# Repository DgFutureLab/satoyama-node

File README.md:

satoyama-node
=============

Satoyama Sensor Network node stack. This stack is designed to connect chibis and sabotens to <a href="https://github.com/DgFutureLab/satoyama-api">Satoyama API</a>. Created by <a href="http://fljapan.com/">Future Lab</a> based on <a href="http://www.freaklabsstore.com">Freaklabs open hardware</a>.

# Prerequisites

## Hardware
(List of provided parts: board, sensors, batteries, etc.)

(NOTE: Add mark on saboten board to connect the FTDI Breakout board in the right direction!!)

## Software
1. Arduino IDE 1.0.6 (Does not work with Arduino 1.5.8 BETA). Get it <a href="http://www.arduino.cc/">here</a>
2. git

# Installation
Follow these steps to set up a Satoyama sensor node!
## Get the code
1. Download this repository: $ git clone https://github.com/DgFutureLab/satoyama-node.git
2. Go into the new directory: $ cd satoyama-node
3. Download all the libraries: $ git pull && git submodule init && git submodule update && git submodule status

## Prepare Arduino libraries

Import the required libraries into your Arduino IDE:  

1. satoyama-libs/SatoyamaChibiLib 
2. satoyama-libs/SdFat 
3. satoyama-libs/chibiArduino-master
4. satoyama-libs/PCF2127
5. satoyama-libs/Humidity_Temperature_Sensor
6. satoyama-libs/NewPing

If you use the standard Arduino GUI, go to Sketch → Import Library → Add Library and select each library name folder.

For the Saboten board: 

1. Copy the folder 'mighty-1284p-freaklabs' inside satoyama-libs to a folder called 'hardware' off your sketches directory, e.g. /Users/maniacbug/Source/Arduino/hardware/mighty-1284p
In a Mac environment: Arduino.app/contents/resources/Java/hardware/
2. Restart the IDE
3. Select Tools > Board > Freaklabs Saboten...

## Prepare the hardware

1. Attach a sonnar, a temperature sensor and a humidity sensor. The pin numbers are specified in <a href="https://github.com/DgFutureLab/satoyama-node/blob/master/SatoyamaChibiLib/config.h">this file</a> (6 for sonar, 0 for temp/humidity)
2. Connect the board to the computer
 
-In case of the Saboten:
Check that the FTDI Breakout board switch is on 5V

3. For OSX users, download the FTDI drivers from http://www.ftdichip.com/Drivers/VCP.htm

4. Open test_saboten/test_saboten.ino (for saboten)
4. Open File>Examples>Chibiarduino-master>4.cmdline (for Chibi)
5. Select your board on the dropdown menu Tool>Board>(FreakLabs Saboten for the saboten) or (Arduino Pro or ProMini (3.3V, 8MHz) w/ATmega328)
6. Upload it to the board
7. Open Arduino IDE's Serial Monitor
8. Set the communication to Carriage return and 57600 baud
9. Set the short address of this collector node by hand writing   *setsaddr* \<address\>  in the serial monitor command prompt. The address should be in HEXADECIMAL. (The address is currently (as of Jan, 2015) set via the script in satoyama-konohana) 
9. Upload collector/collector.ino into your Saboten board. (Include all the necessary libs from third-party-libs folder)

## Setup build system with CMake
Before we wrote the sketches using the Arduino GUI, but now we use standard CMake to generate make files.

1. Install CMake (e.g. brew install cmake on OSX)
2. Change directory into the folder containing the source code that you want to run on the board.
3. mkdir build (all the build files will be stored in this directory)
4. Navigate to build directory: cd build 
5. compile source code and upload to the device: cmake .. -Wno-dev && make && make upload (make sure that the build directory is empty, as CMake will complain otherwise)
6. Use screen to monitor output from the serial device (e.g. tty.usbserial-A501K9HW): /dev/tty.usbserial-A501K9HW 57600,sc8

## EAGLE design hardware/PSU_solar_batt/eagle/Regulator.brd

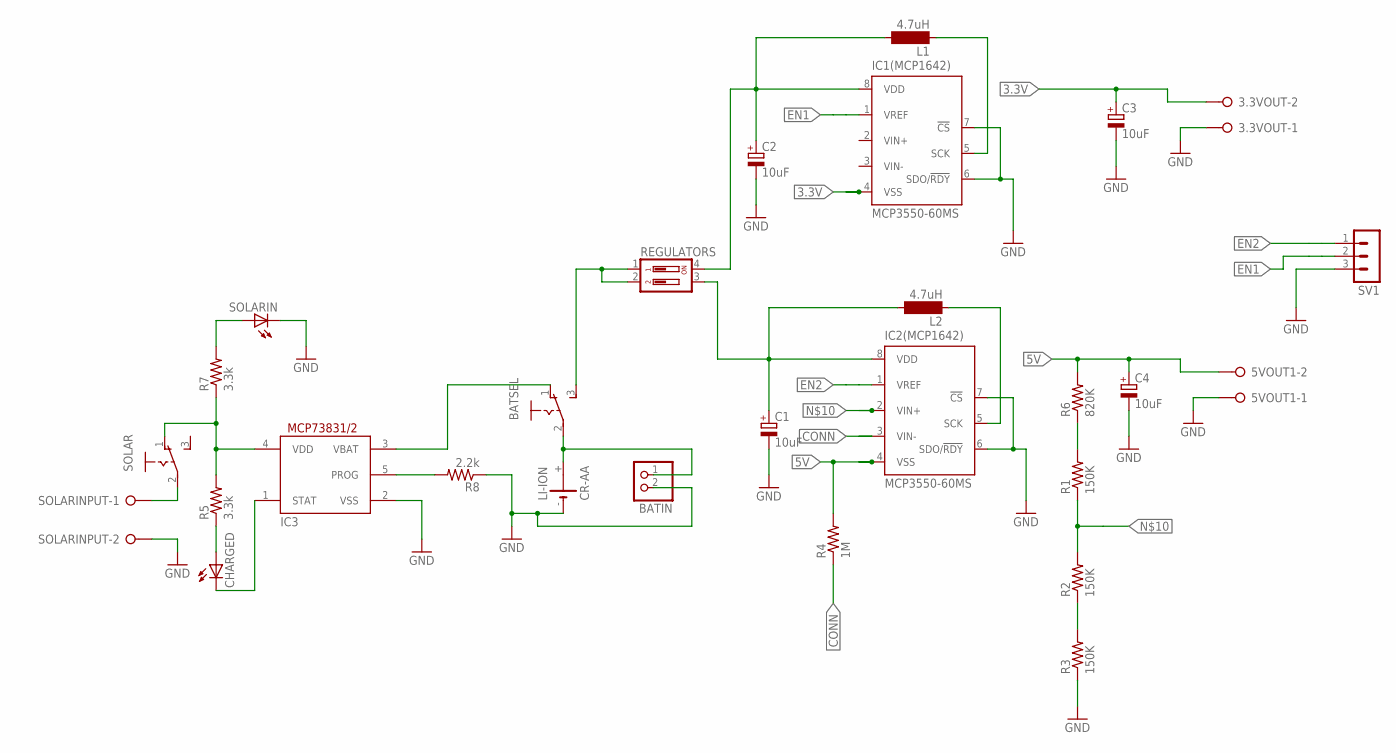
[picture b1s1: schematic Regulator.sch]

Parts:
3.3VOUT, 5VOUT1: W237-02P; W237-132
BATIN: JST_2PIN-THM; JST-PH-2-THM
BATSEL: 255SB
C1, C2, C3, C4: 10uF; 140CLH-1010
CHARGED: LEDCHIP-LED0603; CHIP-LED0603
IC1(MCP1642), IC2(MCP1642): MCP3550-60MS; MSOP8
IC3: MCP73831/OT; SOT23-5L
L1, L2: 4.7uH; MS85
LI-ION: CR-AA; CRAA
R1, R2, R3: 150K; M0805
R4: 1M; M0805
R5, R7: 3.3k; M3216
R6: 820K; M0805
R8: 2.2k; M3216
REGULATORS: DIP02YL
SOLAR: 255SB
SOLARIN: LEDCHIP-LED0603; CHIP-LED0603
SOLARINPUT: W237-02P; W237-132
SV1: MA03-1

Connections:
3.3V: 3.3VOUT.2, C3.+, IC1(MCP1642).4 (VSS)
5V: 5VOUT1.2, C4.+, IC2(MCP1642).4 (VSS), R4.2, R6.2
CONN: IC2(MCP1642).3 (VIN-), R4.1
EN1: IC1(MCP1642).1 (VREF), SV1.2
EN2: IC2(MCP1642).1 (VREF), SV1.1
MCP1642: C2.+, IC1(MCP1642).8 (VDD), L1.2, REGULATORS.4
unnamed: IC1(MCP1642).5 (SCK), L1.1
unnamed: R1.2, R6.1
unnamed: IC2(MCP1642).5 (SCK), L2.1
unnamed: R2.1, R3.2
unnamed: C1.+, IC2(MCP1642).8 (VDD), L2.2, REGULATORS.3
unnamed: IC3.4 (VDD), R5.2, R7.1, SOLAR.1 (O)
unnamed: IC2(MCP1642).2 (VIN+), R1.1, R2.2
unnamed: CHARGED.A, R5.1
unnamed: CHARGED.C, IC3.1 (STAT)
unnamed: BATSEL.3 (S), REGULATORS.1, REGULATORS.2
unnamed: R7.2, SOLARIN.A
unnamed: IC3.5 (PROG), R8.2
unnamed: BATSEL.1 (O), IC3.3 (VBAT)
unnamed: 3.3VOUT.1, 5VOUT1.1, BATIN.2 (1), C1.-, C2.-, C3.-, C4.-, IC1(MCP1642).6 (SDO/!RDY), IC1(MCP1642).7 (!CS), IC2(MCP1642).6 (SDO/!RDY), IC2(MCP1642).7 (!CS), IC3.2 (VSS), LI-ION.-, R3.1, R8.1, SOLARIN.C, SOLARINPUT.2, SV1.3
unnamed: SOLAR.2, SOLARINPUT.1
unnamed: BATIN.1 (2), BATSEL.2, LI-ION.+

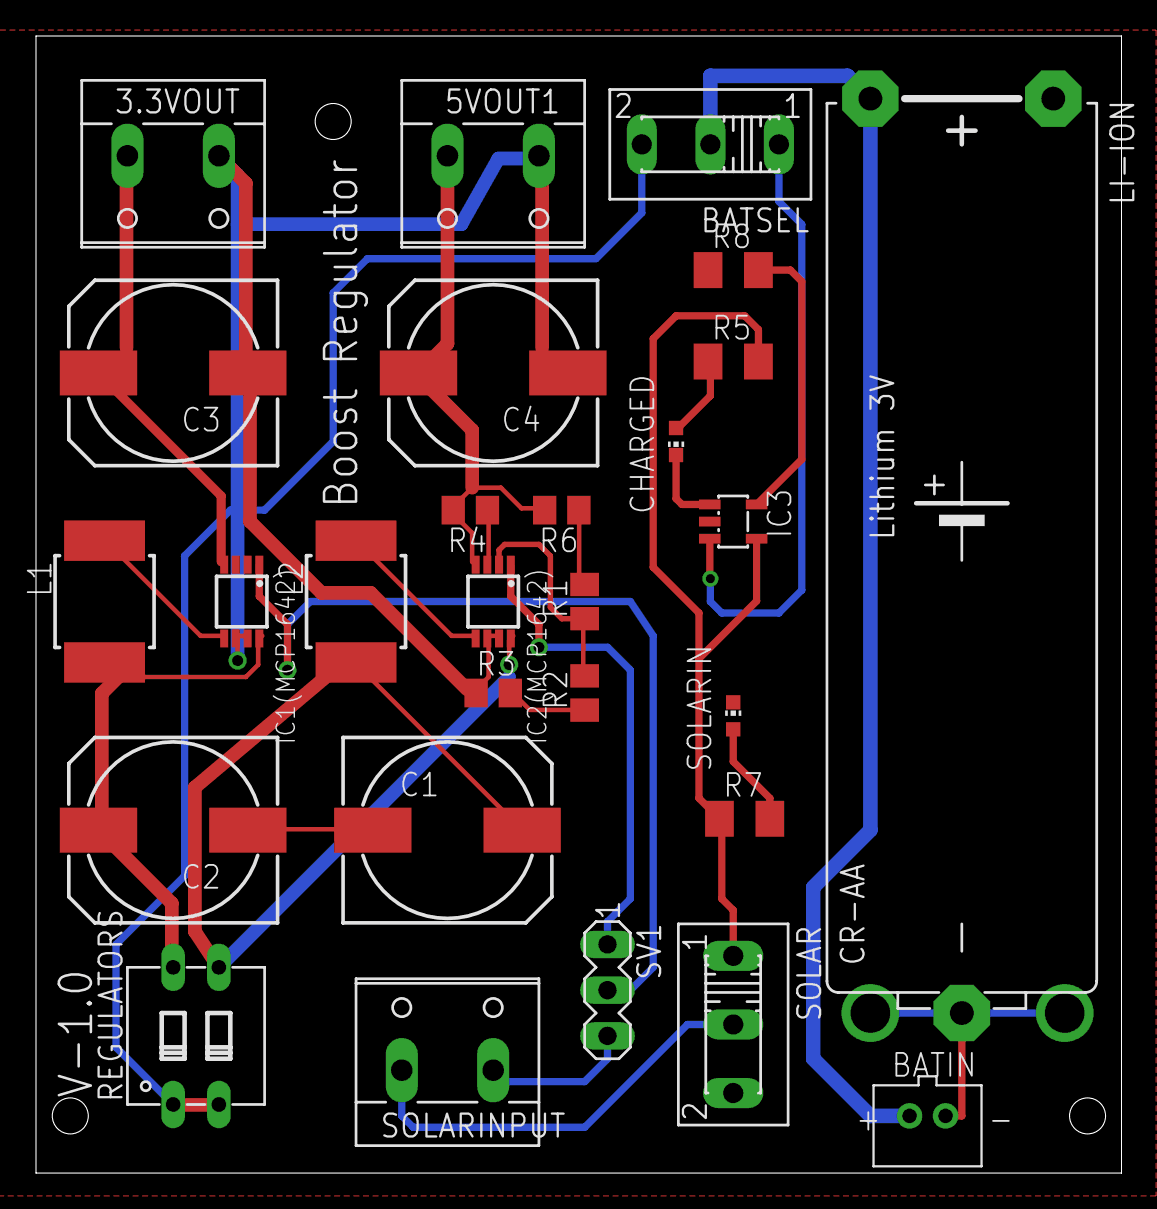
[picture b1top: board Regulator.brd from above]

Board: 2 copper layers, 60.3 x 63.2 mm, 28 parts (0 on the bottom side), 22 nets.

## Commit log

2014-12-03 Collector code
2014-12-03 Arduino library code added
2014-12-05 Moving library
2014-12-05 Cleaning code
2014-12-05 Changing satoyamachibilib defines
2014-12-05 Changed step one
2014-12-16 Adds libs as submodule
2014-12-16 Adds set short address function in collector sketch
2014-12-16 Reverts collector sketch
2014-12-16 deleted third party libs folder
2015-01-07 Fixes path
2015-01-07 Adds pin definitions for VBAT and VSOL
2015-01-07 Creates new ricefield node sketch && renames generic collector sketch to basic
2015-01-07 Fixes cope script
2015-01-08 Sensor node now sends battery voltage as well
2015-01-23 Adds design files for node front
2015-01-23 Adds some sketches for testing the rtc
2015-01-27 Testing second interrupt
2015-01-27 Second interrupt works!
2015-01-27 Interrupt works!! Arduino get it!
2015-01-28 Adds working sleep cycle sketch!
2015-01-28 Saboten is now woken up after 1 minute of sleep
2015-01-29 Adds saboten schematic v1.1
2015-01-30 Instruction for Takachi
2015-02-04 Removes variable number of arguments from sleepRadio function
2015-02-04 Inserts pointer for debugging purposes
2015-02-05 Adding all the power management functions to the collector code
2015-02-05 Remove SatoyamaChibiLib
2015-02-09 Fuck-it-commit. Shit aint working for now.
2015-02-09 Adds CMake script for sleep_cycle program
2015-02-10 Adds header file for sleep cycle program
2015-02-10 Fixes header file. sleep_cycle.cpp now compiles, but all calls to pcf code is commented out
2015-02-10 sleep_cycle now compiles with rtc functions
2015-02-10 Moves around some stuff
2015-02-10 Adds gitignore
2015-02-10 Updates gitignore to ignore all build directories
2015-02-10 Modifies gitignore
2015-02-18 Added description
2015-02-19 Includes temp and sonar libs
2015-02-19 Adds sensor reading to power managed code
2015-02-19 Ricefield sketch compiles, but hangs when trying to transmit data
2015-02-19 BOOM! Working ricefield sketch with power management.
2015-03-03 Cleans and refactors ricefield code
2015-03-25 Surpresses compile time warnings
2015-03-25 Program now uses Saboten library. Confirmed that sleep cycle still works.
2015-03-25 Fixes attachInterrupt in setup && deletes old code
2015-03-25 Adds function to read battery voltage
2015-03-26 Ricefield sketch is now using library function to read battery level
2015-03-26 reicefield program uses cpp lib function
2015-03-26 Removes functions that have been moved to library
2015-03-30 ricefield.cpp works with satoyama-libs da4f78607ab67df42064779d6855fbd5850ac329
2015-03-31 moves board specific setup to board constructor
2015-03-31 Initializes board as pointer
2015-03-31 Refactors and cleans
2015-04-01 ricefield sketch working with satoyama-libs b6a387567a011a091c9add9ea261f50329c236da
2015-04-03 Wifi test
2015-04-07 Removes comments
2015-04-07 Fixes compillation errors
2015-04-08 Adds saboten_sleep sketch (old code, but for reference)
2015-04-08 SD card detection works
2015-04-08 Successfully writes dummy data to SD card
2015-04-09 Fixed bug where file was not opened roperly at random times
2015-04-09 Ricefield sketch now stores battery voltage to SD card
2015-04-10 Adds FILENAME as define in start of program
2015-04-10 Commits changes in satoyama-libs
2015-04-10 Switches to using Saboten function for reading diagnostics (such as voltage level)
2015-04-10 Commits changes in libs
2015-04-10 Finally posting
2015-04-17 Added reading from the actual sensor, and changed to new post and get functions
2015-04-21 Saboten schematics
2015-04-24 Ricefield program with sonar
2015-04-24 Updates libraries
2015-04-27 Checkout here to get code for self-contained sensor node
2015-04-30 adds function for timestamp
2015-04-30 Adds set timestamp function && writes initial time to SD card
2015-04-30 Checkout this commit to get timestamps on data
2015-05-14 Adds sleep loop && memset
2015-05-14 Adds LTSpice simulation of basic negative feedback opamp circuit
2015-05-14 Adds simulation of opamp with bias voltage on positive input
2015-05-19 Adds old arduino version of ricefield sketch for Togas demo at Solid.
2015-05-19 Adds the 3d model of the sonar protector designed by Risa
2015-05-21 Adds chibi version of ricefield sketch. Does not compile with CMake yet though
2015-05-21 Adds snapshots of Daikis first idea for node enclosure
2015-06-08 Adds schematic for TX/RX ultrasonic range finder
2015-06-08 Adds simulation of TX circuit using pulse generator model
2015-06-08 Adds simulation of TX circuit using 555 to generate pulse train
2015-06-09 Renames schematics folder to hardware
2015-06-09 Adds BOM for design1
2015-06-09 Renames folder to simulation
2015-06-09 TX circuit now uses 2N2222 model instead of generic NPN model
2015-06-09 Adds 2N2222 model
2015-06-09 Updates .gitignore to ignore LTSpice aux files
2015-07-17 Adds first ricefield data!!
2015-07-19 Adds schematic/simulation of circuitry to switch between TX and RX modes in the sonar
2015-07-19 Adds TX circuit based on H bridge configuration
2015-07-20 Adds LTSpice file with TX circuit and simulated RX signal, with a signal that switches transducer between TX and RX modes
2015-07-20 Renames signals
2015-07-21 Adds active lowpass filter with cap to remove DC offset from signal
2015-07-21 Fixes faulty wiring of transistor for VCC enable
2015-07-22 Adds first stage amp with LPF, removes unused voltage sources and rearranges
2015-07-24 Moves sd code out of the ricefield sketch
2015-07-24 Removes SD stuff from ricefield sketch
2015-07-25 Adds graphs for water level and battery voltage during first deployment
2015-08-04 Adds sketch that posts data to API
2015-08-04 Removes commented code
2015-08-05 Sketch now serializes data as JSON and can post multiple readings in one HTTP request.
2015-08-14 Adds sketch that slices array. Hopefully this code will be able to solve the Wifi shield crashing, which is probably due to buffer overflow
2015-08-23 Major refactoring and update
2015-08-23 Fixes node_key str concat & misc
2015-09-01 Adds single transducer rx/tx schematic
2015-09-01 Adds schematic for hbridge design. Not used atm and not tested, but I keep it for reference.
2015-09-01 Adds sketch that uses a hardware timer to chirp sonar. This is currently not very useful since the call is blocking, but since it is intended for a single transducer design that might not matter much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
2015-09-07 Adds arduino code for range finder (still untested)
2015-09-15 Adds Risas code for logfam sketch
2015-09-22 Commits ricefield sketch that compiles with newest version of utilsawesome. As of yet untested.
2015-09-23 Arduino ricefield collector now works properly with new version of utilsawesome (tested)
2015-09-23 Cleans ricefield sketch.
2015-09-23 Updates utilsawesome
2015-09-25 Adds sketch to measure if the toilet is occupied or not
2015-09-25 Cleans up toilet sketch
2015-09-25 Toilets sketch now posts occupied/unoccupied to the API
2015-09-28 Changes to using timer interrupts for measuring distance as this is non-blocking
2015-09-30 Adds mouser compatible BOM for PSU
2015-09-30 Adds schematic, board and gerbers
2015-09-30 renames IC1 and IC2 to MCP1642 to avoid confusion (currently MCP3550 part is used instead because MCP1642 is not in the Microchip library)
